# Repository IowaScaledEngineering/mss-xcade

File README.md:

# mss-xcade
Modular Signal System 4 Port Complex Cascade

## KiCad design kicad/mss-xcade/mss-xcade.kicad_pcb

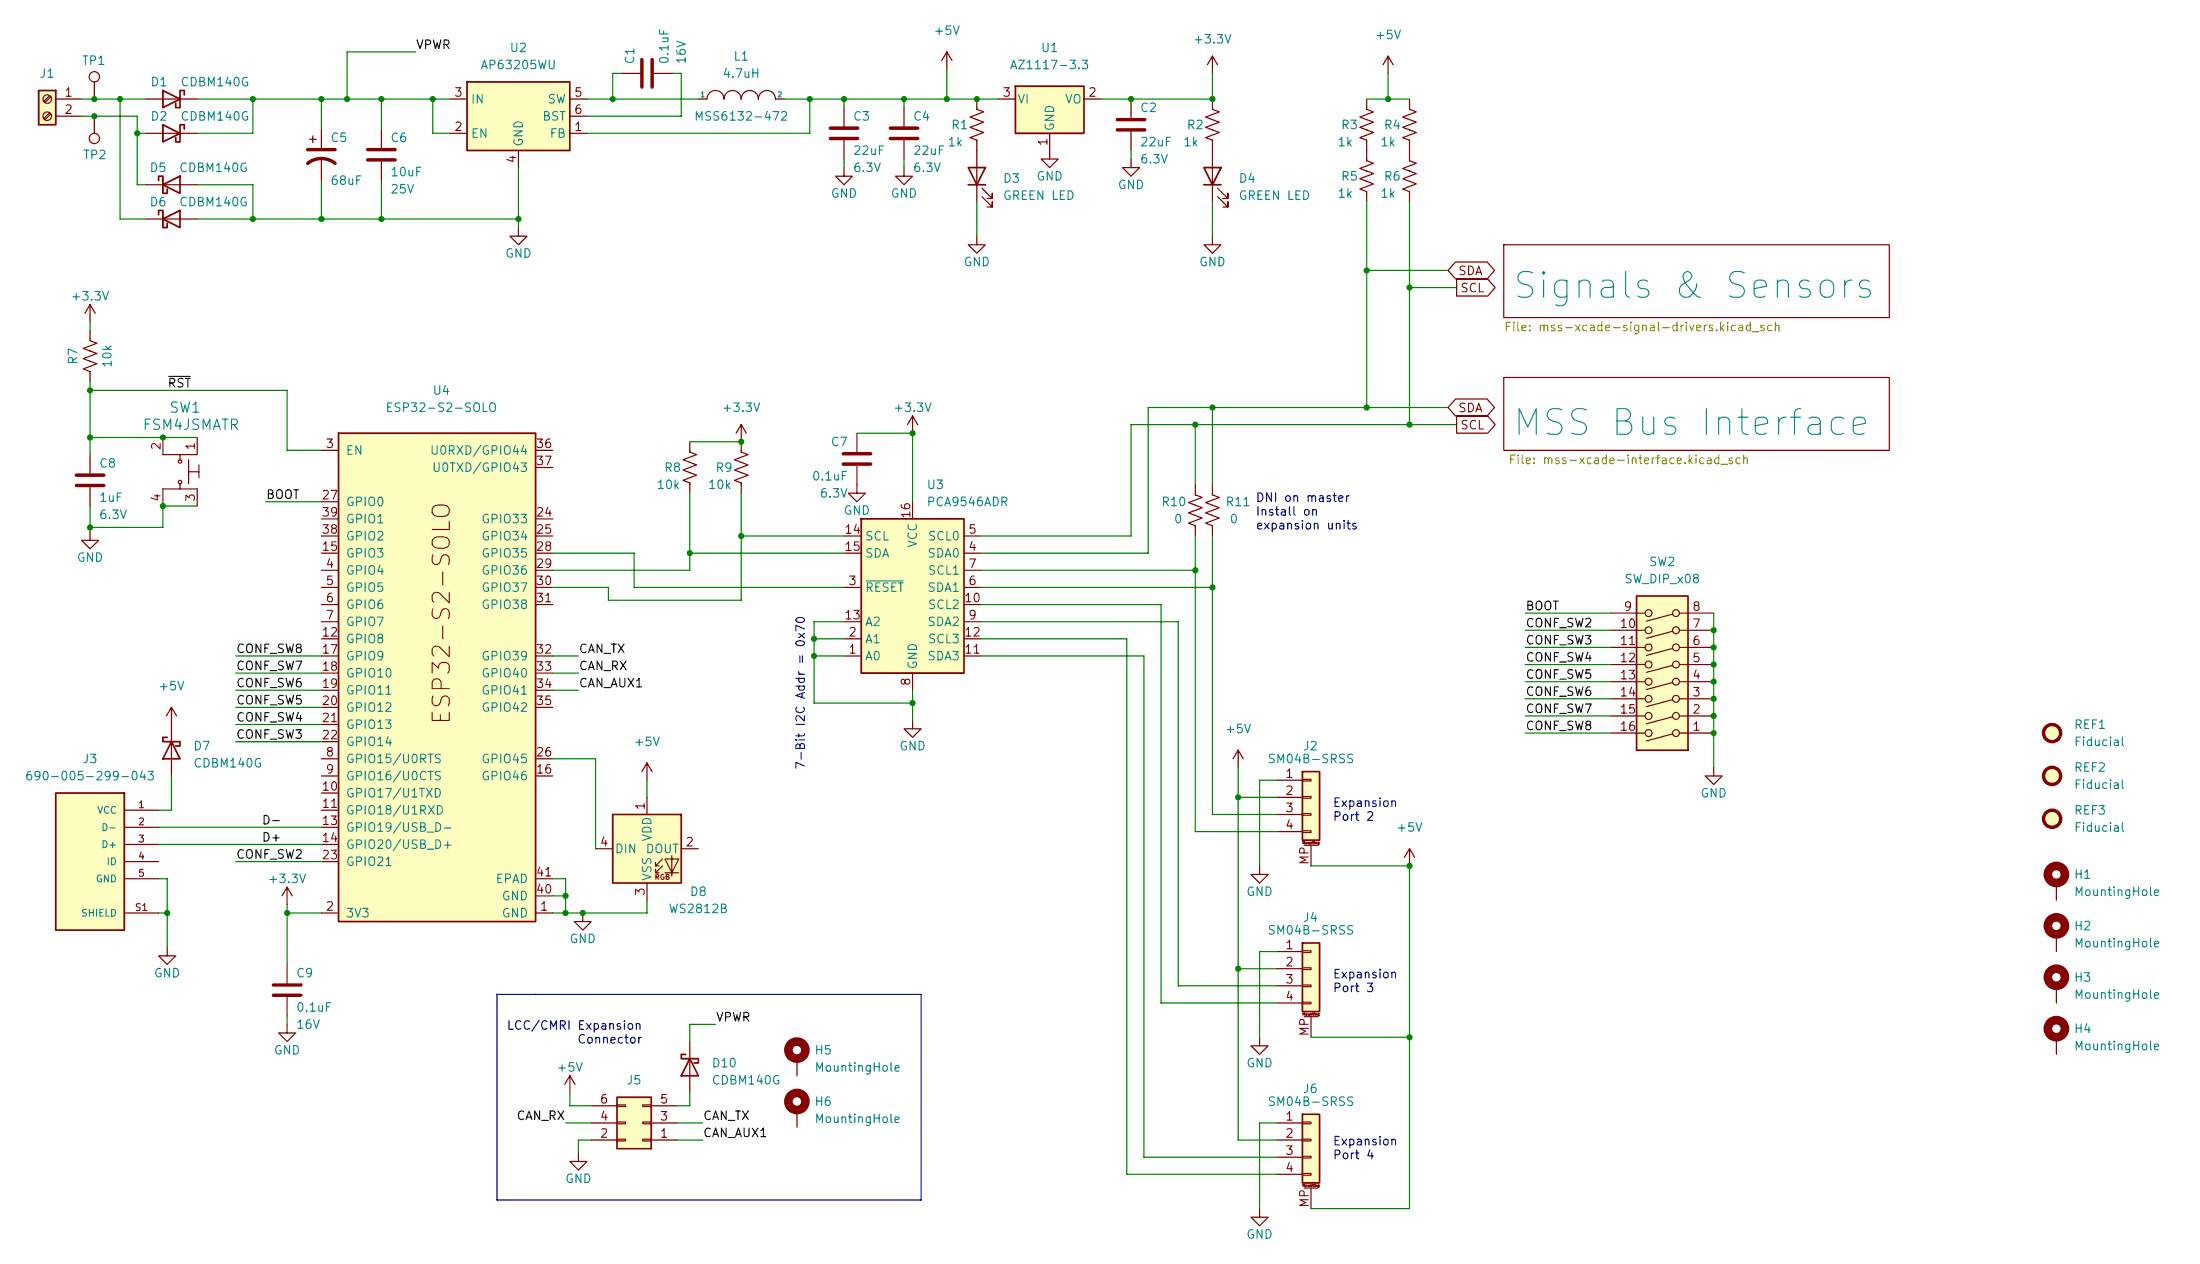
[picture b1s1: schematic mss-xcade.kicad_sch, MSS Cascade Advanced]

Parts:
C1, C9: 0.1uF; C_0805_2012Metric; Voltage 16V
C2, C3, C4: 22uF; C_0805_2012Metric; Voltage 6.3V
C5: 68uF; CP_Elec_6.3x5.8
C6: 10uF; C_0805_2012Metric; Voltage 25V
C7: 0.1uF; C_0805_2012Metric; Voltage 6.3V
C8: 1uF; C_0805_2012Metric; Voltage 6.3V
D1, D2, D5, D6, D7, D10: CDBM140G; SOD-123T
D3, D4: GREEN LED; LED_0805_2012Metric
D8: WS2812B; LED_WS2812B_PLCC4_5.0x5.0mm_P3.2mm
H1, H2, H3, H4: MountingHole; MountingHole_3.2mm_M3_Pad
H5, H6: MountingHole; MountingHole_3.2mm_M3_ISO14580_Pad
J1: Screw_Terminal_01x02; TerminalBlock_RND_205-00012_1x02_P5.00mm_Horizontal
J2, J4, J6: SM04B-SRSS; JST_SH_SM04B-SRSS-TB_1x04-1MP_P1.00mm_Horizontal
J3: 690-005-299-043; EDAC_690-005-299-043; PARTREV 11
J5: Conn_02x03_Odd_Even; PinHeader_2x03_P2.54mm_Vertical
L1: 4.7uH; MSS6132-xxxMLC
R1, R2, R3, R4, R5, R6: 1k; R_0805_2012Metric
R7, R8, R9: 10k; R_0805_2012Metric
R10, R11: 0; R_0805_2012Metric
REF1, REF2, REF3: Fiducial
SW1: FSM4JSMATR; TE_FSM4JSMA; MPN FSM4JSMATR; Digi-Key_PN 450-1759-1-ND
SW2: SW_DIP_x08; SW_DIP_SPSTx08_Slide_6.7x21.88mm_W8.61mm_P2.54mm_LowProfile
TP1, TP2: TestPoint; TestPoint_Pad_D2.0mm
U1: AZ1117-3.3; SOT-223-3_TabPin2
U2: AP63205WU; TSOT-23-6
U3: PCA9546ADR; SOIC-16_3.9x9.9mm_P1.27mm
U4: ESP32-S2-SOLO

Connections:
+3.3V: C2.1, C7.1, C9.1, R2.2, R7.2, R8.2, R9.2, U1.2 (VO), U3.16 (VCC), U4.2 (3V3)
+5V: C3.1, C4.1, D7.1 (K), D8.1 (VDD), J2.2, J2.MP (MountPin), J4.2, J4.MP (MountPin), J5.6, J6.2, J6.MP (MountPin), L1.2, R1.2, R3.2, R4.2, U1.3 (VI), U2.1 (FB); also elsewhere on the board
/BOOT: SW2.9, U4.27 (GPIO0)
/CAN_AUX1: J5.1, U4.34 (GPIO41)
/CAN_RX: J5.4, U4.33 (GPIO40)
/CAN_TX: J5.3, U4.32 (GPIO39)
/CONF_SW2: SW2.10, U4.23 (GPIO21)
/CONF_SW3: SW2.11, U4.22 (GPIO14)
/CONF_SW4: SW2.12, U4.21 (GPIO13)
/CONF_SW5: SW2.13, U4.20 (GPIO12)
/CONF_SW6: SW2.14, U4.19 (GPIO11)
/CONF_SW7: SW2.15, U4.18 (GPIO10)
/CONF_SW8: SW2.16, U4.17 (GPIO9)
/D+: J3.3 (D+), U4.14 (GPIO20/USB_D+)
/D-: J3.2 (D-), U4.13 (GPIO19/USB_D-)
/VPWR: C5.1, C6.1, D1.1 (K), D2.1 (K), D10.1 (K), U2.2 (EN), U2.3 (IN)
/~RST: C8.1, R7.1, SW1.1, SW1.2, U4.3 (EN)
GND: C2.2, C3.2, C4.2, C5.2, C6.2, C7.2, C8.2, C9.2, D3.1 (K), D4.1 (K), D5.2 (A), D6.2 (A), D8.3 (VSS), J2.1, J3.5 (GND), J3.S1 (SHIELD), J4.1, J5.2, J6.1, SW1.3, SW1.4, SW2.1, SW2.2, SW2.3, SW2.4, SW2.5, SW2.6, SW2.7, SW2.8, U1.1 (GND), U2.4 (GND), U3.1 (A0), U3.2 (A1), U3.8 (GND), U3.13 (A2), U4.1 (GND), U4.40 (GND), U4.41 (EPAD); also elsewhere on the board
unnamed: C1.1, L1.1, U2.5 (SW)
unnamed: C1.2, U2.6 (BST)
unnamed: D1.2 (A), D6.1 (K), J1.1, TP1.1
unnamed: D2.2 (A), D5.1 (K), J1.2, TP2.1
unnamed: D3.2 (A), R1.1
unnamed: D4.2 (A), R2.1
unnamed: D7.2 (A), J3.1 (VCC)
unnamed: D8.4 (DIN), U4.26 (GPIO45)
unnamed: D10.2 (A), J5.5
unnamed: J2.3, R11.1, U3.6 (SDA1)
unnamed: J2.4, R10.1, U3.7 (SCL1)
unnamed: J4.3, U3.9 (SDA2)
unnamed: J4.4, U3.10 (SCL2)
unnamed: J6.3, U3.11 (SDA3)
unnamed: J6.4, U3.12 (SCL3)
unnamed: R3.1, R5.2
unnamed: R4.1, R6.2
unnamed: R8.1, U3.15 (SDA), U4.29 (GPIO36)
unnamed: R9.1, U3.14 (SCL), U4.30 (GPIO37)
unnamed: U3.3 (~RESET), U4.28 (GPIO35)
SCL: R6.1, R10.2, U3.5 (SCL0); also elsewhere on the board
SDA: R5.1, R11.2, U3.4 (SDA0); also elsewhere on the board

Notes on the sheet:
LCC/CMRI Expansion Connector
Expansion Port 2
Expansion Port 4
DNI on master Install on expansion units
7-Bit I2C Addr = 0x70
Expansion Port 3

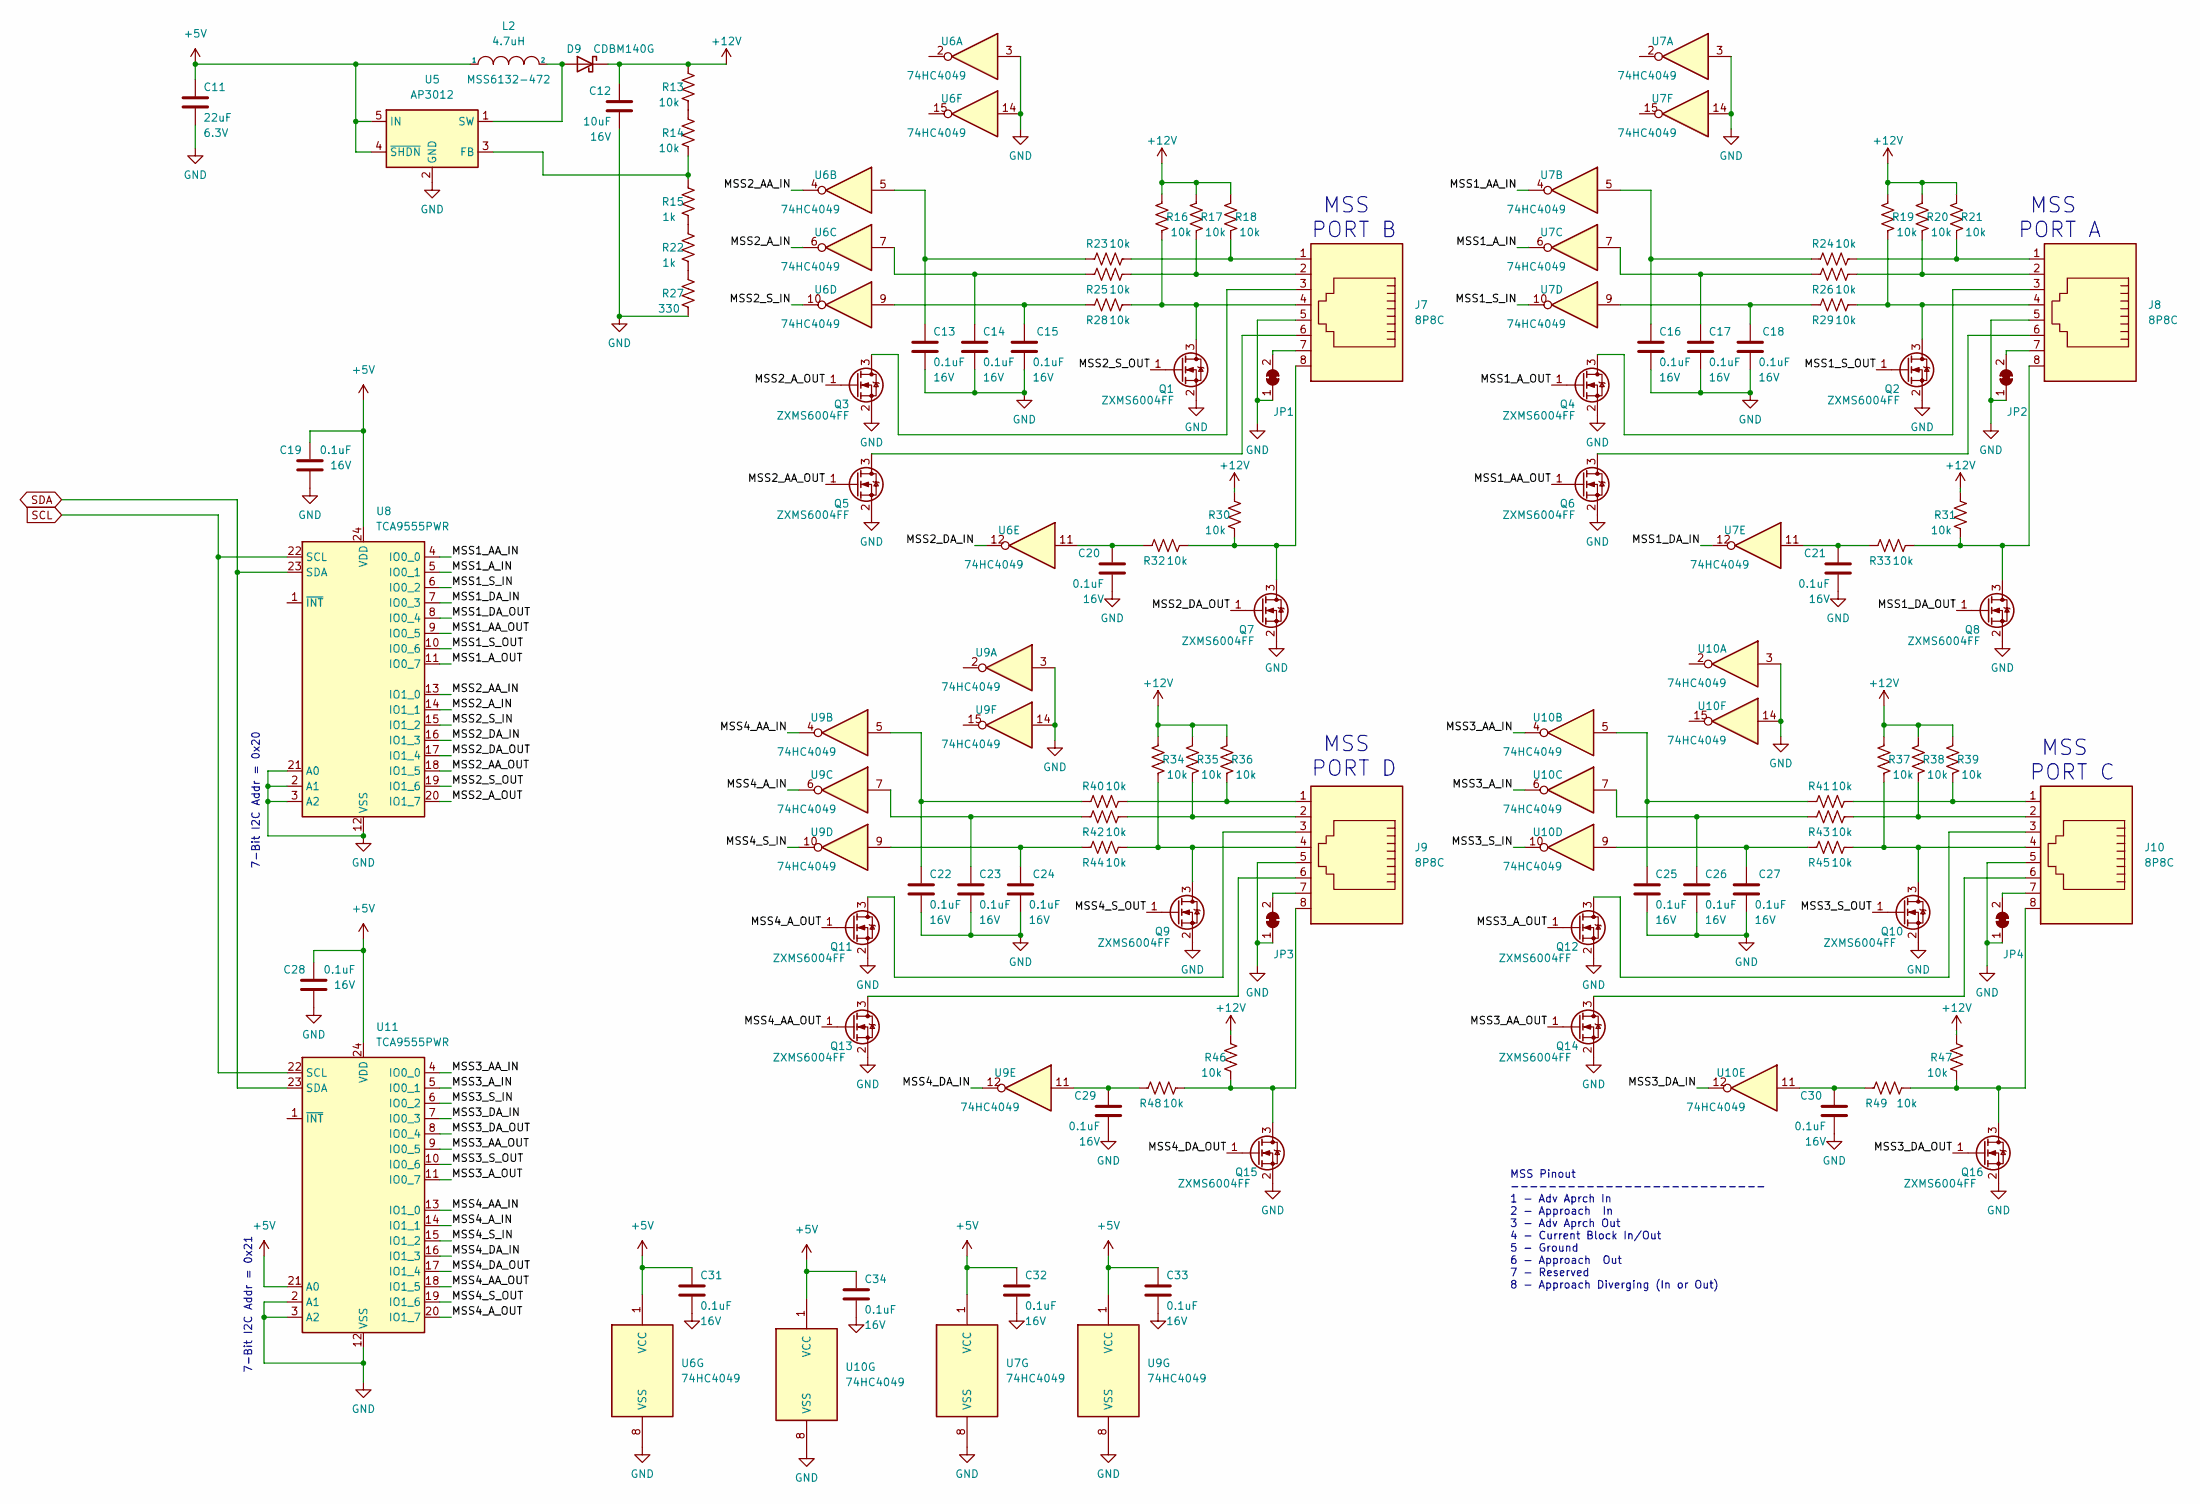
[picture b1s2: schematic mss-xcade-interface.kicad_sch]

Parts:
C11: 22uF; C_0805_2012Metric; Voltage 6.3V
C12: 10uF; C_0805_2012Metric; Voltage 16V
C13, C14, C15, C16, C17, C18, C19, C20, C21, C22, C23, C24, C25, C26, C27, C28, C29, C30, C31, C32, C33, C34: 0.1uF; C_0805_2012Metric; Voltage 16V
D9: CDBM140G; SOD-123T
J7, J8, J9, J10: 8P8C; RJ45_Amphenol_54602-x08_Horizontal
JP1, JP2, JP3, JP4: SolderJumper_2_Bridged; SolderJumper-2_P1.3mm_Bridged_RoundedPad1.0x1.5mm
L2: 4.7uH; MSS6132-xxxMLC
Q1, Q2, Q3, Q4, Q5, Q6, Q7, Q8, Q9, Q10, Q11, Q12, Q13, Q14, Q15, Q16: ZXMS6004FF; SOT-23
R13, R14, R16, R17, R18, R19, R20, R21, R23, R24, R25, R26, R28, R29, R30, R31, R32, R33, R34, R35, R36, R37, R38, R39, R40, R41, R42, R43, R44, R45, R46, R47, R48, R49: 10k; R_0805_2012Metric
R15, R22: 1k; R_0805_2012Metric
R27: 330; R_0805_2012Metric
U5: AP3012; SOT-23-5
U6, U7, U9, U10: 74HC4049; SO-16_3.9x9.9mm_P1.27mm
U8, U11: TCA9555PWR; TSSOP-24_4.4x7.8mm_P0.65mm

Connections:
+5V: C11.1, C19.1, C28.1, C31.1, C32.1, C33.1, C34.1, L2.1, U5.4 (~SHDN), U5.5 (IN), U6.1 (VCC), U7.1 (VCC), U8.24 (VDD), U9.1 (VCC), U10.1 (VCC), U11.21 (A0), U11.24 (VDD); also elsewhere on the board
+12V: C12.1, D9.1 (K), R13.2, R16.2, R17.2, R18.2, R19.2, R20.2, R21.2, R30.2, R31.2, R34.2, R35.2, R36.2, R37.2, R38.2, R39.2, R46.2, R47.2
/MSS Bus Interface/MSS1_AA_IN: U7.4, U8.4 (IO0_0)
/MSS Bus Interface/MSS1_AA_OUT: Q6.1 (G), U8.9 (IO0_5)
/MSS Bus Interface/MSS1_A_IN: U7.6, U8.5 (IO0_1)
/MSS Bus Interface/MSS1_A_OUT: Q4.1 (G), U8.11 (IO0_7)
/MSS Bus Interface/MSS1_DA_IN: U7.12, U8.7 (IO0_3)
/MSS Bus Interface/MSS1_DA_OUT: Q8.1 (G), U8.8 (IO0_4)
/MSS Bus Interface/MSS1_S_IN: U7.10, U8.6 (IO0_2)
/MSS Bus Interface/MSS1_S_OUT: Q2.1 (G), U8.10 (IO0_6)
/MSS Bus Interface/MSS2_AA_IN: U6.4, U8.13 (IO1_0)
/MSS Bus Interface/MSS2_AA_OUT: Q5.1 (G), U8.18 (IO1_5)
/MSS Bus Interface/MSS2_A_IN: U6.6, U8.14 (IO1_1)
/MSS Bus Interface/MSS2_A_OUT: Q3.1 (G), U8.20 (IO1_7)
/MSS Bus Interface/MSS2_DA_IN: U6.12, U8.16 (IO1_3)
/MSS Bus Interface/MSS2_DA_OUT: Q7.1 (G), U8.17 (IO1_4)
/MSS Bus Interface/MSS2_S_IN: U6.10, U8.15 (IO1_2)
/MSS Bus Interface/MSS2_S_OUT: Q1.1 (G), U8.19 (IO1_6)
/MSS Bus Interface/MSS3_AA_IN: U10.4, U11.4 (IO0_0)
/MSS Bus Interface/MSS3_AA_OUT: Q14.1 (G), U11.9 (IO0_5)
/MSS Bus Interface/MSS3_A_IN: U10.6, U11.5 (IO0_1)
/MSS Bus Interface/MSS3_A_OUT: Q12.1 (G), U11.11 (IO0_7)
/MSS Bus Interface/MSS3_DA_IN: U10.12, U11.7 (IO0_3)
/MSS Bus Interface/MSS3_DA_OUT: Q16.1 (G), U11.8 (IO0_4)
/MSS Bus Interface/MSS3_S_IN: U10.10, U11.6 (IO0_2)
/MSS Bus Interface/MSS3_S_OUT: Q10.1 (G), U11.10 (IO0_6)
/MSS Bus Interface/MSS4_AA_IN: U9.4, U11.13 (IO1_0)
/MSS Bus Interface/MSS4_AA_OUT: Q13.1 (G), U11.18 (IO1_5)
/MSS Bus Interface/MSS4_A_IN: U9.6, U11.14 (IO1_1)
/MSS Bus Interface/MSS4_A_OUT: Q11.1 (G), U11.20 (IO1_7)
/MSS Bus Interface/MSS4_DA_IN: U9.12, U11.16 (IO1_3)
/MSS Bus Interface/MSS4_DA_OUT: Q15.1 (G), U11.17 (IO1_4)
/MSS Bus Interface/MSS4_S_IN: U9.10, U11.15 (IO1_2)
/MSS Bus Interface/MSS4_S_OUT: Q9.1 (G), U11.19 (IO1_6)
GND: C11.2, C12.2, C13.2, C14.2, C15.2, C16.2, C17.2, C18.2, C19.2, C20.2, C21.2, C22.2, C23.2, C24.2, C25.2, C26.2, C27.2, C28.2, C29.2, C30.2, C31.2, C32.2, C33.2, C34.2, J7.5, J8.5, J9.5, J10.5, JP1.1 (A), JP2.1 (A), JP3.1 (A), JP4.1 (A), Q1.2 (S), Q2.2 (S), Q3.2 (S), Q4.2 (S), Q5.2 (S), Q6.2 (S), Q7.2 (S), Q8.2 (S), Q9.2 (S), Q10.2 (S), Q11.2 (S), Q12.2 (S), Q13.2 (S), Q14.2 (S), Q15.2 (S), Q16.2 (S), R27.1, U5.2 (GND), U6.3, U6.8 (VSS), U6.14, U7.3, U7.8 (VSS), U7.14, U8.2 (A1), U8.3 (A2), U8.12 (VSS), U8.21 (A0), U9.3, U9.8 (VSS), U9.14, U10.3, U10.8 (VSS), U10.14, U11.2 (A1), U11.3 (A2), U11.12 (VSS); also elsewhere on the board
unnamed: C13.1, R23.2, U6.5
unnamed: C14.1, R25.2, U6.7
unnamed: C15.1, R28.2, U6.9
unnamed: C16.1, R24.2, U7.5
unnamed: C17.1, R26.2, U7.7
unnamed: C18.1, R29.2, U7.9
unnamed: C20.1, R32.2, U6.11
unnamed: C21.1, R33.2, U7.11
unnamed: C22.1, R40.2, U9.5
unnamed: C23.1, R42.2, U9.7
unnamed: C24.1, R44.2, U9.9
unnamed: C25.1, R41.2, U10.5
unnamed: C26.1, R43.2, U10.7
unnamed: C27.1, R45.2, U10.9
unnamed: C29.1, R48.2, U9.11
unnamed: C30.1, R49.2, U10.11
unnamed: D9.2 (A), L2.2, U5.1 (SW)
unnamed: J7.1, R18.1, R23.1
unnamed: J7.2, R17.1, R25.1
unnamed: J7.3, Q3.3 (D)
unnamed: J7.4, Q1.3 (D), R16.1, R28.1
unnamed: J7.6, Q5.3 (D)
unnamed: J7.7, JP1.2 (B)
unnamed: J7.8, Q7.3 (D), R30.1, R32.1
unnamed: J8.1, R21.1, R24.1
unnamed: J8.2, R20.1, R26.1
unnamed: J8.3, Q4.3 (D)
unnamed: J8.4, Q2.3 (D), R19.1, R29.1
unnamed: J8.6, Q6.3 (D)
unnamed: J8.7, JP2.2 (B)
unnamed: J8.8, Q8.3 (D), R31.1, R33.1
unnamed: J9.1, R36.1, R40.1
unnamed: J9.2, R35.1, R42.1
unnamed: J9.3, Q11.3 (D)
unnamed: J9.4, Q9.3 (D), R34.1, R44.1
unnamed: J9.6, Q13.3 (D)
unnamed: J9.7, JP3.2 (B)
unnamed: J9.8, Q15.3 (D), R46.1, R48.1
unnamed: J10.1, R39.1, R41.1
unnamed: J10.2, R38.1, R43.1
unnamed: J10.3, Q12.3 (D)
unnamed: J10.4, Q10.3 (D), R37.1, R45.1
unnamed: J10.6, Q14.3 (D)
unnamed: J10.7, JP4.2 (B)
unnamed: J10.8, Q16.3 (D), R47.1, R49.1
unnamed: R13.1, R14.2
unnamed: R14.1, R15.2, U5.3 (FB)
unnamed: R15.1, R22.2
unnamed: R22.1, R27.2
SCL: U8.22 (SCL), U11.22 (SCL); also elsewhere on the board
SDA: U8.23 (SDA), U11.23 (SDA); also elsewhere on the board

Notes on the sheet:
MSS PORT A
7-Bit I2C Addr = 0x20
MSS Pinout --------------------------- 1 - Adv Aprch In 2 - Approach In 3 - Adv Aprch Out 4 - Current Block In/Out 5 - Ground 6 - Approach Out 7 - Reserved 8 - Approach Diverging (In or Out)
7-Bit I2C Addr = 0x21
MSS PORT B
MSS PORT D
MSS PORT C

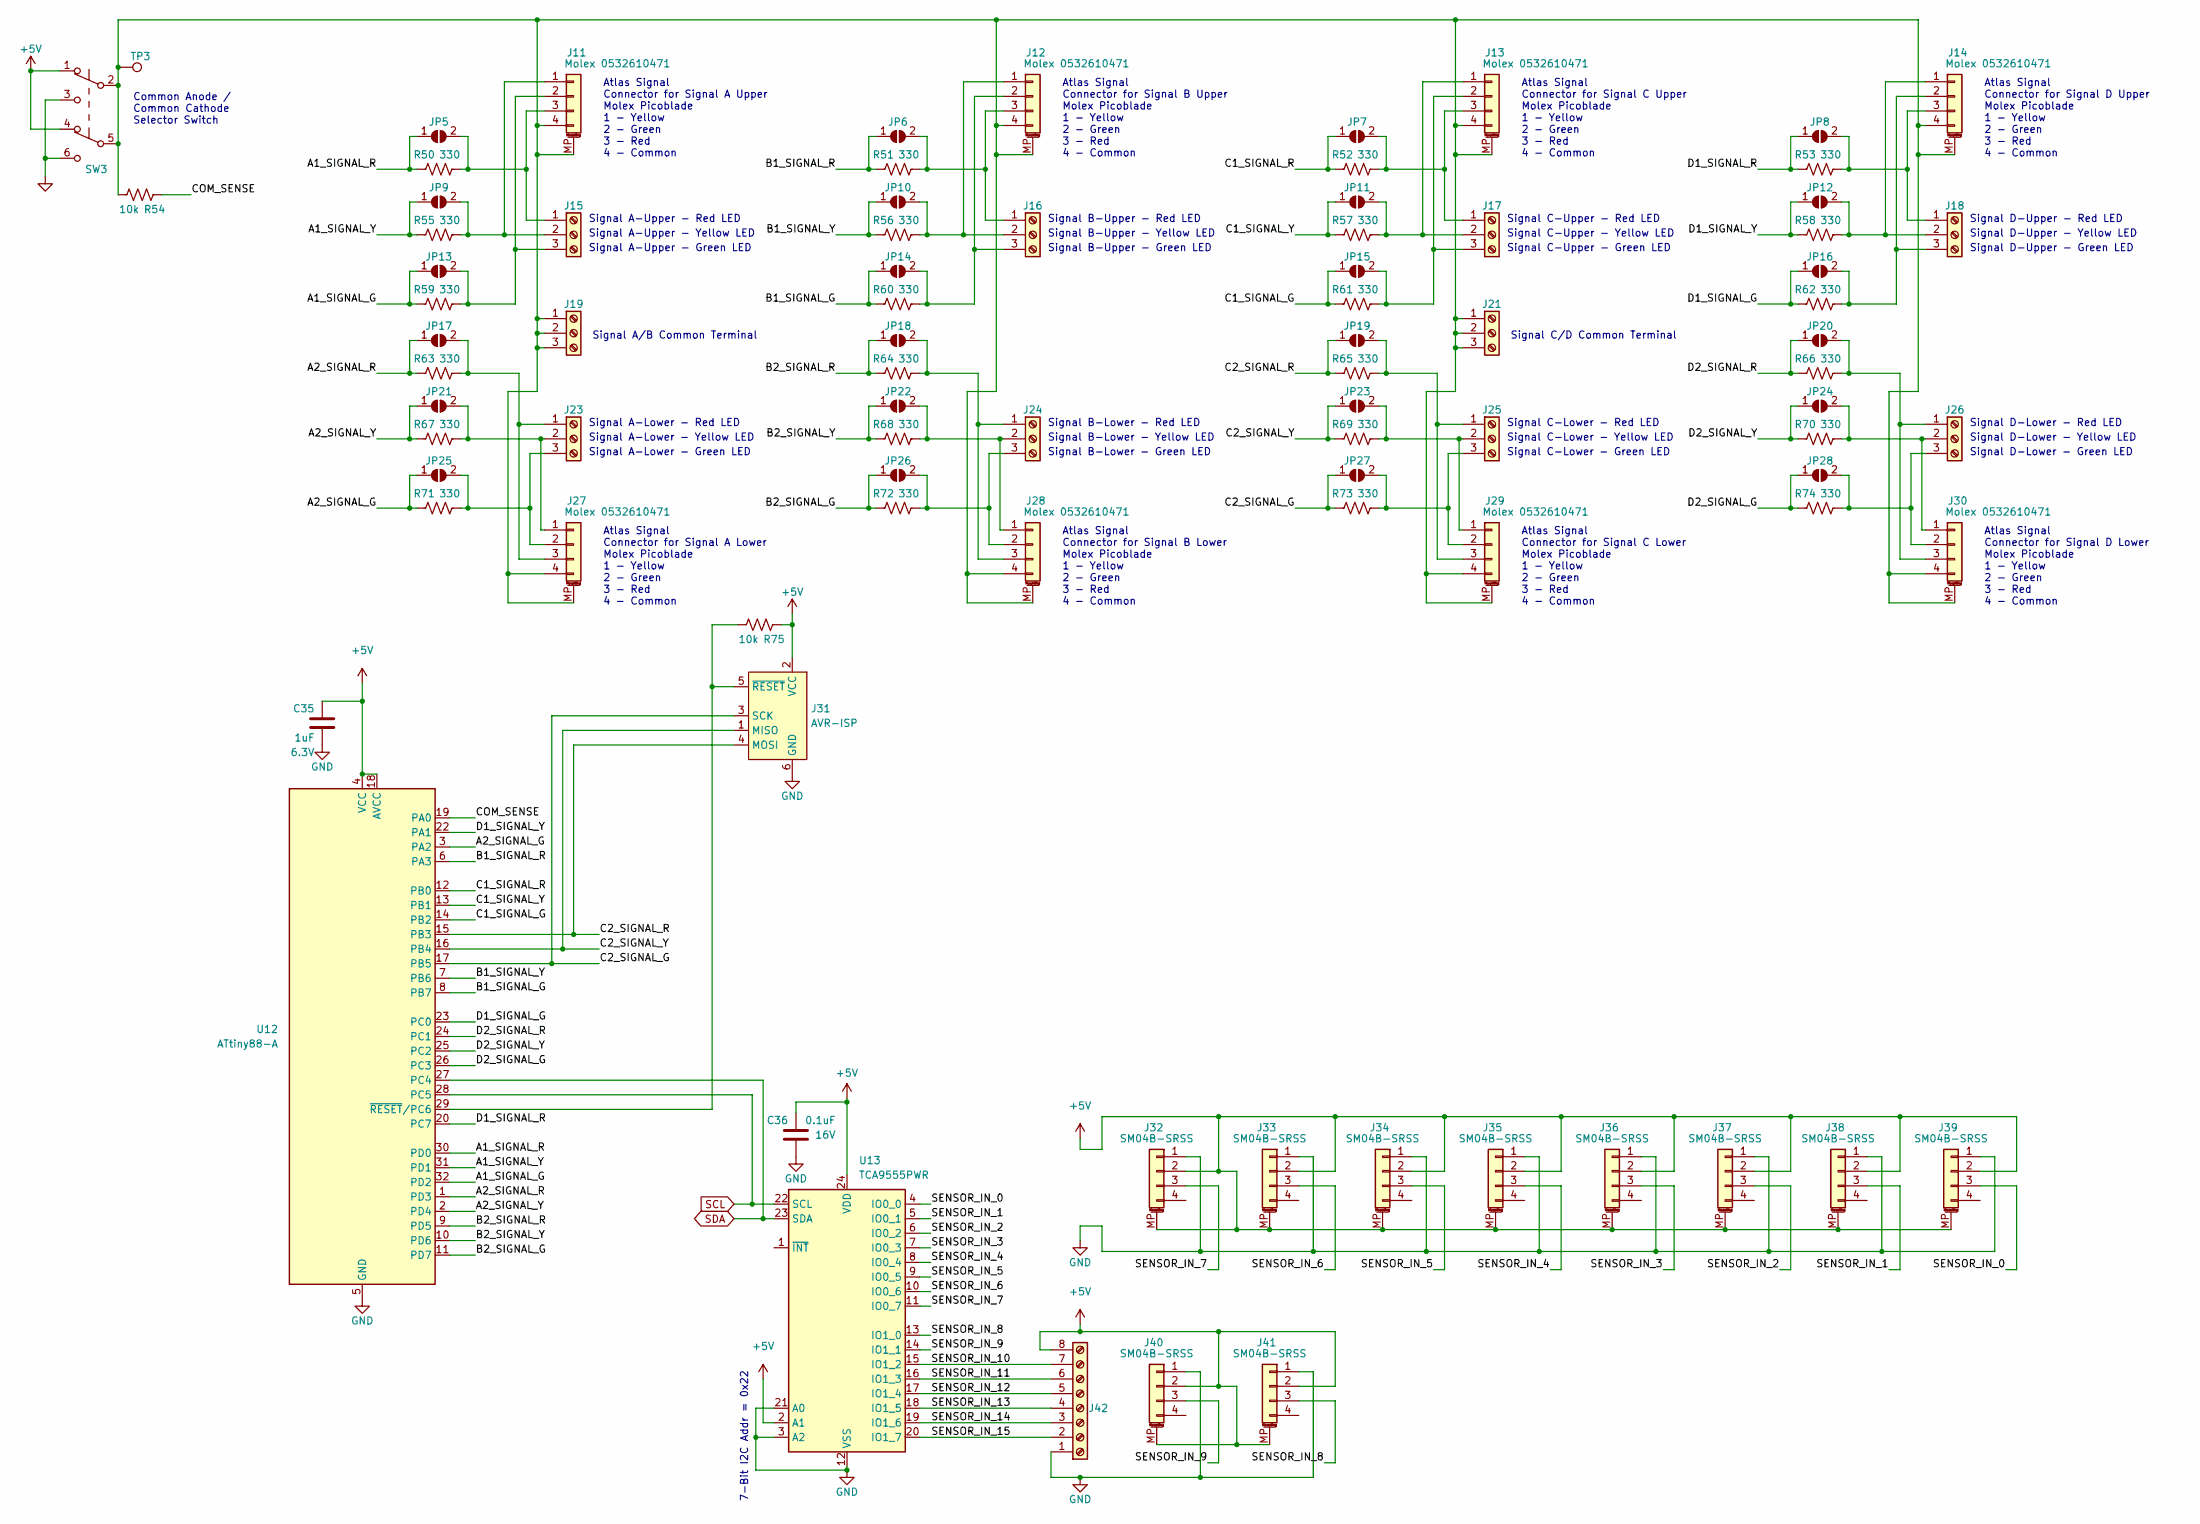
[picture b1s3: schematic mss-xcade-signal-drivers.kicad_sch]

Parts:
C35: 1uF; C_0805_2012Metric; Voltage 6.3V
C36: 0.1uF; C_0805_2012Metric; Voltage 16V
J11, J12, J13, J14, J27, J28, J29, J30: Molex 0532610471; Molex_PicoBlade_53261-0471_1x04-1MP_P1.25mm_Horizontal
J15, J16, J17, J18, J19, J21, J23, J24, J25, J26: Screw_Terminal_01x02; TerminalBlock_MetzConnect_Type059_RT06303HBWC_1x03_P3.50mm_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
J31: AVR-ISP; Tag-Connect_TC2030-IDC-NL_2x03_P1.27mm_Vertical
J32, J33, J34, J35, J36, J37, J38, J39, J40, J41: SM04B-SRSS; JST_SH_SM04B-SRSS-TB_1x04-1MP_P1.00mm_Horizontal
J42: Screw_Terminal_01x08; TerminalBlock_TE_282834-8_1x08_P2.54mm_Horizontal
JP5, JP6, JP7, JP8, JP9, JP10, JP11, JP12, JP13, JP14, JP15, JP16, JP17, JP18, JP19, JP20, JP21, JP22, JP23, JP24, JP25, JP26, JP27, JP28: SolderJumper_2_Open; SolderJumper-2_P1.3mm_Open_RoundedPad1.0x1.5mm
R50, R51, R52, R53, R55, R56, R57, R58, R59, R60, R61, R62, R63, R64, R65, R66, R67, R68, R69, R70, R71, R72, R73, R74: 330; R_0805_2012Metric
R54, R75: 10k; R_0805_2012Metric
SW3: JS202011SCQN; SW_JS202011SCQN
TP3: TestPoint; TestPoint_Pad_D2.0mm
U12: ATtiny88-A; TQFP-32_7x7mm_P0.8mm
U13: TCA9555PWR; TSSOP-24_4.4x7.8mm_P0.65mm

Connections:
+5V: C35.1, C36.1, J31.2 (VCC), J32.2, J32.MP (MountPin), J33.2, J33.MP (MountPin), J34.2, J34.MP (MountPin), J35.2, J35.MP (MountPin), J36.2, J36.MP (MountPin), J37.2, J37.MP (MountPin), J38.2, J38.MP (MountPin), J39.2, J39.MP (MountPin), J40.2, J40.MP (MountPin), J41.2, J41.MP (MountPin), J42.8, R75.1, SW3.1 (A), SW3.4 (A), U12.4 (VCC), U12.18 (AVCC), U13.2 (A1), U13.24 (VDD); also elsewhere on the board
/Signals & Sensors/A1_SIGNAL_G: JP13.1 (A), R59.1, U12.32 (PD2)
/Signals & Sensors/A1_SIGNAL_R: JP5.1 (A), R50.1, U12.30 (PD0)
/Signals & Sensors/A1_SIGNAL_Y: JP9.1 (A), R55.1, U12.31 (PD1)
/Signals & Sensors/A2_SIGNAL_G: JP25.1 (A), R71.1, U12.3 (PA2)
/Signals & Sensors/A2_SIGNAL_R: JP17.1 (A), R63.1, U12.1 (PD3)
/Signals & Sensors/A2_SIGNAL_Y: JP21.1 (A), R67.1, U12.2 (PD4)
/Signals & Sensors/B1_SIGNAL_G: JP14.1 (A), R60.1, U12.8 (PB7)
/Signals & Sensors/B1_SIGNAL_R: JP6.1 (A), R51.1, U12.6 (PA3)
/Signals & Sensors/B1_SIGNAL_Y: JP10.1 (A), R56.1, U12.7 (PB6)
/Signals & Sensors/B2_SIGNAL_G: JP26.1 (A), R72.1, U12.11 (PD7)
/Signals & Sensors/B2_SIGNAL_R: JP18.1 (A), R64.1, U12.9 (PD5)
/Signals & Sensors/B2_SIGNAL_Y: JP22.1 (A), R68.1, U12.10 (PD6)
/Signals & Sensors/C1_SIGNAL_G: JP15.1 (A), R61.1, U12.14 (PB2)
/Signals & Sensors/C1_SIGNAL_R: JP7.1 (A), R52.1, U12.12 (PB0)
/Signals & Sensors/C1_SIGNAL_Y: JP11.1 (A), R57.1, U12.13 (PB1)
/Signals & Sensors/C2_SIGNAL_G: J31.3 (SCK), JP27.1 (A), R73.1, U12.17 (PB5)
/Signals & Sensors/C2_SIGNAL_R: J31.4 (MOSI), JP19.1 (A), R65.1, U12.15 (PB3)
/Signals & Sensors/C2_SIGNAL_Y: J31.1 (MISO), JP23.1 (A), R69.1, U12.16 (PB4)
/Signals & Sensors/COM_SENSE: R54.1, U12.19 (PA0)
/Signals & Sensors/D1_SIGNAL_G: JP16.1 (A), R62.1, U12.23 (PC0)
/Signals & Sensors/D1_SIGNAL_R: JP8.1 (A), R53.1, U12.20 (PC7)
/Signals & Sensors/D1_SIGNAL_Y: JP12.1 (A), R58.1, U12.22 (PA1)
/Signals & Sensors/D2_SIGNAL_G: JP28.1 (A), R74.1, U12.26 (PC3)
/Signals & Sensors/D2_SIGNAL_R: JP20.1 (A), R66.1, U12.24 (PC1)
/Signals & Sensors/D2_SIGNAL_Y: JP24.1 (A), R70.1, U12.25 (PC2)
/Signals & Sensors/SENSOR_IN_0: J39.3, U13.4 (IO0_0)
/Signals & Sensors/SENSOR_IN_1: J38.3, U13.5 (IO0_1)
/Signals & Sensors/SENSOR_IN_2: J37.3, U13.6 (IO0_2)
/Signals & Sensors/SENSOR_IN_3: J36.3, U13.7 (IO0_3)
/Signals & Sensors/SENSOR_IN_4: J35.3, U13.8 (IO0_4)
/Signals & Sensors/SENSOR_IN_5: J34.3, U13.9 (IO0_5)
/Signals & Sensors/SENSOR_IN_6: J33.3, U13.10 (IO0_6)
/Signals & Sensors/SENSOR_IN_7: J32.3, U13.11 (IO0_7)
/Signals & Sensors/SENSOR_IN_8: J41.3, U13.13 (IO1_0)
/Signals & Sensors/SENSOR_IN_9: J40.3, U13.14 (IO1_1)
/Signals & Sensors/SENSOR_IN_10: J42.7, U13.15 (IO1_2)
/Signals & Sensors/SENSOR_IN_11: J42.6, U13.16 (IO1_3)
/Signals & Sensors/SENSOR_IN_12: J42.5, U13.17 (IO1_4)
/Signals & Sensors/SENSOR_IN_13: J42.4, U13.18 (IO1_5)
/Signals & Sensors/SENSOR_IN_14: J42.3, U13.19 (IO1_6)
/Signals & Sensors/SENSOR_IN_15: J42.2, U13.20 (IO1_7)
GND: C35.2, C36.2, J31.6 (GND), J32.1, J33.1, J34.1, J35.1, J36.1, J37.1, J38.1, J39.1, J40.1, J41.1, J42.1, SW3.3 (C), SW3.6 (C), U12.5 (GND), U12.21 (GND), U13.3 (A2), U13.12 (VSS), U13.21 (A0); also elsewhere on the board
unnamed: J11.1, J15.2, JP9.2 (B), R55.2
unnamed: J11.2, J15.3, JP13.2 (B), R59.2
unnamed: J11.3, J15.1, JP5.2 (B), R50.2
unnamed: J11.4, J11.MP (MountPin), J12.4, J12.MP (MountPin), J13.4, J13.MP (MountPin), J14.4, J14.MP (MountPin), J19.1, J19.2, J19.3, J21.1, J21.2, J21.3, J27.4, J27.MP (MountPin), J28.4, J28.MP (MountPin), J29.4, J29.MP (MountPin), J30.4, J30.MP (MountPin), R54.2, SW3.2 (B), SW3.5 (B), TP3.1
unnamed: J12.1, J16.2, JP10.2 (B), R56.2
unnamed: J12.2, J16.3, JP14.2 (B), R60.2
unnamed: J12.3, J16.1, JP6.2 (B), R51.2
unnamed: J13.1, J17.2, JP11.2 (B), R57.2
unnamed: J13.2, J17.3, JP15.2 (B), R61.2
unnamed: J13.3, J17.1, JP7.2 (B), R52.2
unnamed: J14.1, J18.2, JP12.2 (B), R58.2
unnamed: J14.2, J18.3, JP16.2 (B), R62.2
unnamed: J14.3, J18.1, JP8.2 (B), R53.2
unnamed: J23.1, J27.3, JP17.2 (B), R63.2
unnamed: J23.2, J27.1, JP21.2 (B), R67.2
unnamed: J23.3, J27.2, JP25.2 (B), R71.2
unnamed: J24.1, J28.3, JP18.2 (B), R64.2
unnamed: J24.2, J28.1, JP22.2 (B), R68.2
unnamed: J24.3, J28.2, JP26.2 (B), R72.2
unnamed: J25.1, J29.3, JP19.2 (B), R65.2
unnamed: J25.2, J29.1, JP23.2 (B), R69.2
unnamed: J25.3, J29.2, JP27.2 (B), R73.2
unnamed: J26.1, J30.3, JP20.2 (B), R66.2
unnamed: J26.2, J30.1, JP24.2 (B), R70.2
unnamed: J26.3, J30.2, JP28.2 (B), R74.2
unnamed: J31.5 (~RESET), R75.2, U12.29 (~RESET/PC6)
SCL: U12.28 (PC5), U13.22 (SCL); also elsewhere on the board
SDA: U12.27 (PC4), U13.23 (SDA); also elsewhere on the board

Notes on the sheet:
Atlas Signal Connector for Signal C Lower Molex Picoblade 1 - Yellow 2 - Green 3 - Red 4 - Common
Signal B-Lower - Green LED
Signal C-Lower - Red LED
Signal C/D Common Terminal
Signal C-Upper - Red LED
Signal C-Upper - Green LED
Signal D-Upper - Yellow LED
Signal D-Lower - Red LED
Signal C-Lower - Green LED
Signal D-Upper - Red LED
Signal B-Upper - Green LED
Signal A-Upper - Yellow LED
Signal C-Upper - Yellow LED
Signal B-Upper - Red LED
Atlas Signal Connector for Signal D Lower Molex Picoblade 1 - Yellow 2 - Green 3 - Red 4 - Common
Atlas Signal Connector for Signal B Upper Molex Picoblade 1 - Yellow 2 - Green 3 - Red 4 - Common
Atlas Signal Connector for Signal A Upper Molex Picoblade 1 - Yellow 2 - Green 3 - Red 4 - Common
Atlas Signal Connector for Signal D Upper Molex Picoblade 1 - Yellow 2 - Green 3 - Red 4 - Common
Signal D-Lower - Yellow LED
Atlas Signal Connector for Signal B Lower Molex Picoblade 1 - Yellow 2 - Green 3 - Red 4 - Common
Signal A/B Common Terminal
Atlas Signal Connector for Signal A Lower Molex Picoblade 1 - Yellow 2 - Green 3 - Red 4 - Common
Signal D-Upper - Green LED
Signal D-Lower - Green LED
7-Bit I2C Addr = 0x22
Signal C-Lower - Yellow LED
Signal A-Upper - Red LED
Signal B-Lower - Yellow LED
Signal A-Lower - Yellow LED
Signal A-Lower - Green LED
Signal A-Lower - Red LED
Signal B-Lower - Red LED
Signal B-Upper - Yellow LED
Common Anode / Common Cathode Selector Switch
Atlas Signal Connector for Signal C Upper Molex Picoblade 1 - Yellow 2 - Green 3 - Red 4 - Common
Signal A-Upper - Green LED

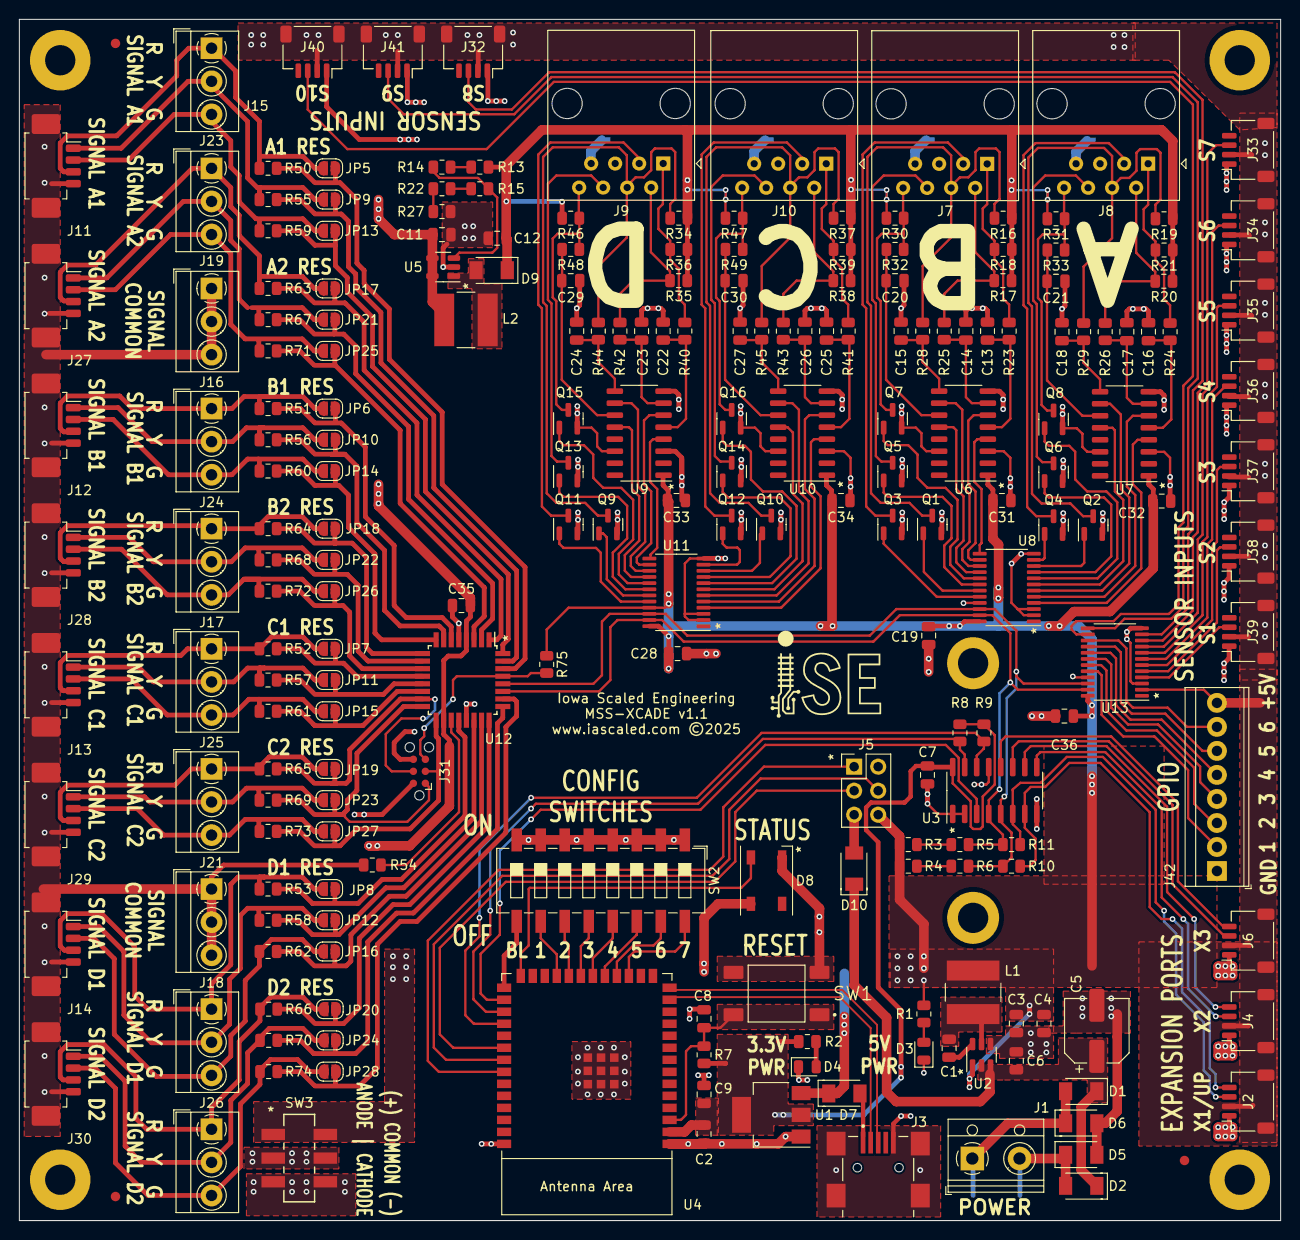
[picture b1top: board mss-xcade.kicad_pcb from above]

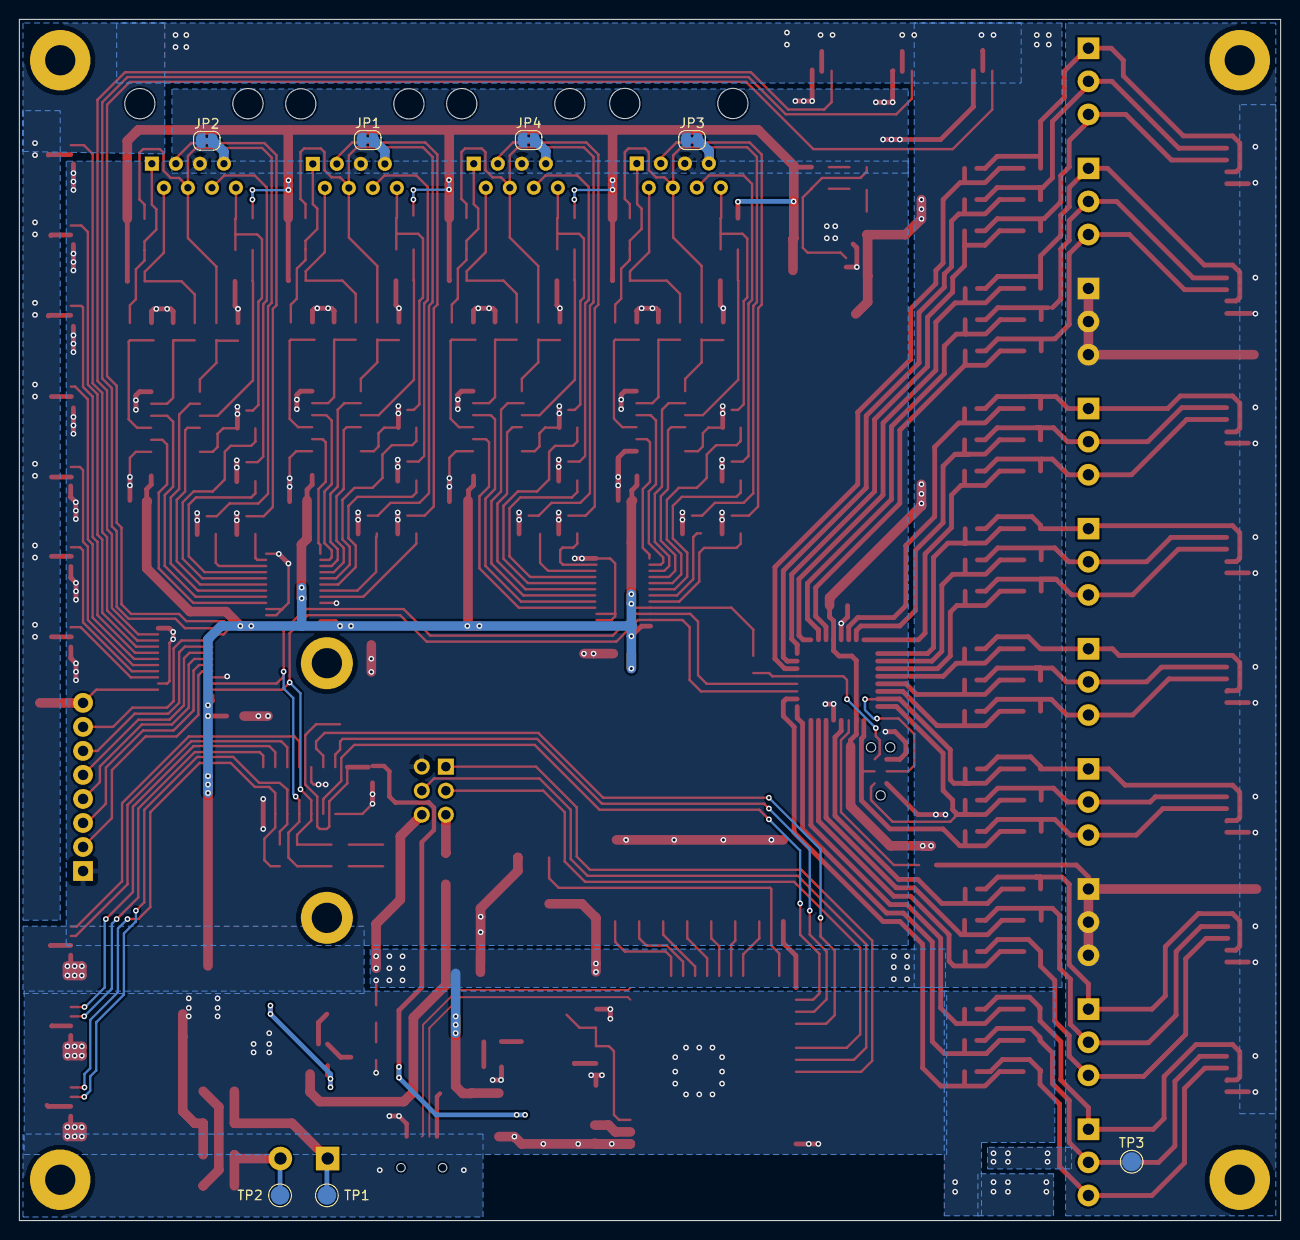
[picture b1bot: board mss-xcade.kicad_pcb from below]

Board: 2 copper layers, 133.4 x 127.0 mm, 233 parts (7 on the bottom side), 189 nets.

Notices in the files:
src/i2c-shcp/i2c-shcp.c:
License:  GNU General Public License v3
LICENSE:
Copyright (C) 2025 Michael Petersen & Nathan Holmes
kicad/mss-xcade-can/mss-xcade-can.kicad_pcb:
www.iascaled.com ©2025
